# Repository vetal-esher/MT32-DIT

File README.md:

# MT32-DIT
<h3>Adding digital output to legendary Roland MT-32</h3>
<p>Project status: ⬛⬛⬛⬛⬛⬛⬛⬛⬛⬛⬛⬛⬜ 95%</p>
<p>
This project can be considered part #2 of the digitalization of old synthesizers. In the first part I described <a href="https://github.com/vetal-esher/18bit-DIT">how you can add a  digital outpu</a>t to almost any synthesizer (where the DAC circuit uses standard L/R combined I2S) by using the AK4103AVF</p>

<p>
Roland MT-32, familiar to old gamers in the 90s and very rare now, is an even older device that uses a parallel DAC scheme that was 
quite common in Roland's D-series, which does not just convert the final stereo stream in-line, but also simultaneously performs 
the services of a DAC for the reverb IC.</p>

<h3>Digging demuxer logic</h4>

<p>
It turns out that we do not have direct access to the digital stream containing the final audio data. The PCM54HP receives a stream 
that sequentially contains not only clean left and right channels, but also separate reverb data for the left and right channels. 
It looks something like this (all frames are 16bit, order is assumed): [RSYN1][LSYN1][REV R][REV L][RSYN2][LSYN2][RSYN1][LSYN1][REV R][REV L][RSYN2] [LSYN2] etc.</p>
<p>
The advantage of a parallel DAC is that it works instantly, i.e. there is no delay at all in taking the current values 
from the (essentially) resistor assembly and the next moment doing the task of transforming a completely different picture. <strong>Edit: 
to tell the truth, there IS small delay required to let the output settled the final value.</strong>
</p>
<p>The widely known CD4051 is engaged in demultiplexing all this porridge of audio data. Channel switching in the CD4051 is carried out 
through the control lines mixed from LA and Reverb chips SH1 SH2 SH2 (SH - Sample / Hold), as well as the INH line, which turns on and off 
all channels. At the output of the demuxer, three pairs of analog channels are formed, which are then mixed and undergo final 
processing in a low-pass filter. The LP filter should have a flat amplitude response in the 0-20kHz range and a high attenuation above 20kHz.
</p>

<p>
Bit depth and sampling frequency of MT-32 according to the declared characteristics - 15bit 32kHz. In the first version of MT-32 
(the so-called "old"), the last (actually, LSB) 16th bit at the PCM54HP input is shorted to ground, and for that (15bit) reason the 14th bit fell out 
in the data bus itself (counting from zero). However, for us, the frame width will always be 16 bits (the 2nd MT-32 version has full 16bit bus). Theoretically, the channel  switching frequency 0-1-2-3-4-5-6-7 each time triggers a 0/1 state change in control signal A, so you can 
expect 128kHz on this line,  64kHz on line B, and C with 32kHz respectively. But we don't know the order of the frames. Even if we 
sequentially record all the states of the parallel bus, it will be useless if we do not know the order of switching ABC. In practice, 
without a three-channel oscilloscope, you can try to catch the states of at least two of the three lines (A and C), and then record 
the AB and BC, A and INH sequences in order to further bring the picture into one.
</p>

<p>

So now we know the frame order: [L REV][RSYN2][LSYN2][R REV][RSYN1][LSYN1], [L REV][RSYN2][LSYN2][R REV][RSYN1][LSYN1] .. etc. 
If you listen to these pins in analog, it becomes clear that SYN1 is a clean signal, REV is a reverb return. SYN2 appears to be 
analog as well, but too quiet to be recorded legibly; but since SYN2 is also mixed into the final mix, we'll do that too. 
By the way, if you look at the unused outputs of the CD4051 CH4 and CH5, there will be [almost] crisp 32kHz:

<p>The INH control signal operates at a frequency of 256kHz, which means we will need to read all ports at this frequency. 
Disabling all channels is necessary so that there is no false triggering on rising edges @ABC states, when INH=1 tells us that 
we don’t need to send anything to serial. With INH=0, we must read the bus, and depending on the states of ABC, scatter it to 
the appropriate output. Ideally, we need to define the beginning of frame (we take the highest INH peak for the reference frame)
and mix all L / R frames into two final ones. But for the test, you can start by sending two frames with a clean non-reverberated 
information (RSYN1, LSYN1). At first I thought to bother with the sequence' start detection, but then I omitted this part, because,
even if the logic begins to run in the middle, defining LSYN1 as the end of the sequence we will reset the counters and then start 
working in the correct order. The logic in this case will look something like this (I will use a pseudo-language here with a syntax 
that is clear to everyone):</p>

<pre>
(R,L)=(0,0);
(FLAG_RSYN1,FLAG_LSYN1,FLAG_RSYN2,FLAG_LSYN2,FLAG_RREV,FLAG_LREV)=(0,0,0,0,0,0);
(RSYN1,LSYN1,RSYN2,LSYN2,RREV,LREV)=(0,0,0,0,0,0);
while (256kHz_cycle) {
	input=read(PCM54_parallel);
	A=read(CD4051_A); B=read(CD4051_B); C=read(CD4051_C); INH=read(CD4051_INH);

	#INH==0 enables output
	if (INH==0) {
		if (A==1 && B==1 && C==0) {
			RSYN2=input; FLAG_RSYN2=1; #RSYN2
		}
		elsif (A==0 && B==1 && C==0) {
			LSYN2=input; FLAG_LSYN2=1; #LSYN2
		}
		elsif (A==0 && B==0 && C==1) {
			RREV=input; FLAG_RREV=1;   #RREV
		}
		elsif (A==0 && B==0 && C==0) {
			LREV=input; FLAG_LREV=1;   #LREV
		}
		elsif (A==1 && B==1 && C==1) {
			RSYN1=input; FLAG_RSYN1=1; #RSYN1
		}
		elsif (A==0 && B==1 && C==1) {
			LSYN1=input; 		   #LSYN1 this is the last channel in frame
			(FLAG_RSYN1,FLAG_LSYN1,FLAG_RSYN2,FLAG_LSYN2,FLAG_RREV,FLAG_LREV)=(1,1,1,1,1,1);
		}

		if (FLAG_RSYN1==1 && FLAG_LSYN1==1 && FLAG_RSYN2==1 && FLAG_LSYN2==1 && FLAG_RREV==1 && FLAG_LREV==1) {

			#in merge there will be magic
			L=merge(LSYN1,LSYN2,LREV);
			R=merge(RSYN1,RSYN2,RREV);
			write_serial(R,L); 

			#reset channel flags
			(FLAG_RSYN1,FLAG_LSYN1,FLAG_RSYN2,FLAG_LSYN2,FLAG_RREV,FLAG_LREV)=(0,0,0,0,0,0);
		}
	}
}
</pre>

<h3>Hardware part</h3>

<p>Schematically, the plan of the entire project was drawn like this:</p>

<p>
There is only one magic figure involved in this plan, and here, I will honestly say, giant constructions of logic which must perform the task of mixing digital streams comes to mind. I was told that I should stop doing garbage and learn a programmable FPGA. All of the DAC and INH/A/B/C signals are CMOS-level, so we need to convert them to TTL by CD4050B. By the way, we will get fixed levels of INH after CD4050:
</p>

<h4>DIT</h4>
<p>
Since we are dealing with 16 bits, a large number of DITs can be used, as they all work at least with 16-bit RJ. For these purposes, I chose DIT4192, because I have it  already available after experimenting with the 18-bit DIT, but you can skip mounting 4192 if you don't have it (details below). Settings are typical:
<table border="1">
<tr><th colspan="2">DIT4192 Hardware mode</th></tr>
<tr><td>Mode operation</td><td>Slave (SYNC and SCLK are inputs)</td></tr>
<tr><td>Format</td><td>16-Bit Right-Justified</td></tr>
<tr><td>Sampling frequency</td><td>32kHz</td></tr>
<tr><td>Master clock</td><td>16.384MHz (512*fs)</td></tr>
<tr><td>Bit clock</td><td>1.024MHz (16*2*32KHz)</td></tr>
</table>
</p>

<h3>Magic part</h3>
<p>The FPGA <a href="https://wiki.sipeed.com/hardware/en/tang/Tang-Nano-9K/Nano-9K.html">TangNano9K</a> was chosen for the magic part, so the "profit" plan was drawn:</p>

<p>And then the complete schematic of the "magic" part was done. Note the I2S connector, you can completely skip DIT4192 in schematic and use your favorite external DIT, or even just transport I2S to I2S receiver. I tested I2S with external WM8804 DIT board and it works perfectly.</p>

<h3>Making prototypes</h3>
<p>I started with sandwich-like breadboard, trying to split the CMOS-TTL logic from TangNano. Different methods, using couple of variants (voltage dividers) and CD4050 were tried..</p>

.. and then, when i finally decided to use CD4050, i have projected the PCB. The PCBs were made quick at PCBway factory, and i must say their quality is awesome, even for such pet projects like mine :) 

<p>Final design assumes, that the original PCM54HP will be desoldered from MT-32 mainboard, and then socketed on second footprint right on DIT pcb. After that, MT32-DIT can be soldered or socketed on MT-32 mainboard. But for now, we'll just put on the DIT board right over PCM54HP IC.</p>

<h2>Partlist</h2>
<table border=1>
	<tr><th>Reference</th><th>Total</th><th>Value</th><th>Package</th></tr>
	<tr><td>X1</td><td>1</td><td>16.384MHz</td><td>Oscillator DIP-8</td></tr>
	<tr><td>U1, U2, U3, U5</td><td>4</td><td>CD4050</td><td>SO-16</td></tr>
	<tr><td>U4</td><td>1</td><td>Gowin 9K</td><td></td></tr>
	<tr><td>U6</td><td>1</td><td>PCM54HP**</td><td>DIP-28</td></tr>
	<tr><td>U8</td><td>1</td><td>DIT4192IPW***</td><td>SSOP-28</td></tr>
	<tr><td>U7</td><td>1</td><td>AP1117-33</td><td>SOT223-3_TABPIN2</td></tr>
	<tr><td>U10</td><td>2</td><td>PinHeader 1x28</td><td>P2.54mm</td></tr>
	<tr><td>T1</td><td>1</td><td>PE-65612NL***</td><td>PE-65612NL</td></tr>
	<tr><td>SW1</td><td>1</td><td>PWR SW</td><td>SW_DIP_SPSTx01_P2.54mm</td></tr>
	<tr><td>SW2</td><td>1</td><td>CFG SW***</td><td>SW_DIP_SPSTx05_P2.54mm</td></tr>
	<tr><td>R1, R2, R4, R5, R6, R7, R8</td><td>7</td><td>10K ***</td><td>0402</td></tr>
	<tr><td>R3</td><td>1</td><td>300R ***</td><td>0402</td></tr>
	<tr><td>J1</td><td>1</td><td>PinHeader 1x04</td><td>P2.54mm</td></tr>
	<tr><td>J2, J3***</td><td>2</td><td>PinHeader 1x02</td><td>P2.54mm</td></tr>
	<tr><td>J4</td><td></td><td>DNP*</td><td></td></tr>
	<tr><td>J5</td><td>1</td><td>PinHeader 1x05</td><td>P2.54mm</td></tr>
	<tr><td>C1, C2, C3, C4, C5, C6, C7, C8, C10, C11, C12***, C13***, C14</td><td>13</td><td>0.1uF</td><td>0402</td></tr>
	<tr><td>C15***</td><td>1</td><td>10uF</td><td>0402</td></tr>
	<tr><td>C9</td><td>1</td><td>10-22uF</td><td>CP_EIA-7343-43</td></tr>
</table>
<p>If only specific component can be skipped, it's marked within "Reference" column, otherwise all components can be skipped if mark is in "Value" column.</p>
<p><strong>*</strong> - Do Not Place</p>
<p><strong>**</strong> - optional, no need if DIT pcb soldered on top of the original DAC</p>
<p><strong>***</strong> - optional, no need if DIT4192 is not available and you use external DIT</p>

<h3>Learning VERILOG</h3>

<p>I did not have any experience in designing FPGA projects, and did not knew about verilog language anything. But it appeared, that my pseudo-language logic described above is almost verilog-like! So, after few weeks, the very first working code was written.</p>

<details>
  <summary>First verilog code:</summary>	

<pre>
module top (
        input mclk,             //master clock //pin 51
        input clk_inh,          //256kHz INH clk input //pin 53
        input [2:0] ch_id,      //cd4051 sample/hold controls a/b/c 128/64/32kHz //pin a 77 b 76 c 48
        input [15:0] dac,       //parallel input from dac
	input sys_rst_n,        //reset input
	output wire dtr,        //data ready flag //pin54
        output sdata,           //16bit i2s sdata output  //pin 49
        output wire wclk,       //i2s word select lrck output 32kHz //pin 31
        output wire bck         //i2s bit clock output 1024MHz //pin32
);

wire [31:0] data;

dac_decoder dac1(
	.clk_inh(clk_inh),.ch_id(ch_id),.dac(dac),.data(data),.rst_n(sys_rst_n),.dtr(dtr)
);

i2s_serializer ser1 (
	.mclk(mclk),.sdata(sdata),.wclk(wclk),.bck(bck),.data(data),.rst_n(sys_rst_n)
);

endmodule

module i2s_serializer (
        input mclk,             	//master clock 16.384MHz
	input [31:0] data,		//input channels register 
	input wire rst_n,		//reset button	
	output reg sdata,   	    	//i2s sdata output
        output reg wclk,        	//i2s word select lrck output mclk/512 = 32kHz
        output wire bck         	//[3] bit'mclk. i2s bit clock output 
					//16bit * 2 * 32000 = 1.024 MHz (16.384/16)
);
reg [31:0] mclk_counter;       		//32bit counter
assign bck=mclk_counter[3];     	//1.024MHz divide
reg [31:0] data_buf;			//i2s output buffer 
reg [4:0] cbit;				//0-15 current bit counter
			
initial begin
	mclk_counter<=0; cbit<=0; wclk<=0; data_buf<=0;
end

always  @(posedge mclk,negedge rst_n) begin
	if(!rst_n) begin mclk_counter<=0; end 
	else begin mclk_counter<=mclk_counter+1; end
end

//i2s WCLK=0 left, =1 right
always  @(negedge bck) begin					//send sdata from buffer
	if (wclk==0) begin sdata<=data_buf[31-cbit]; end 	//LSYN send
	else if (wclk==1) begin sdata<=data_buf[15-cbit]; end	//RSYN send
	cbit<=cbit+4'b01;
	if (cbit==15 && wclk==0) 
		begin cbit<=0; wclk<=1; end			//LSYN1 end
	else if (cbit==15 && wclk==1) 
		begin cbit<=0; wclk<=0; data_buf<=data; end 	//RSYN1 end, new buffer read
end
endmodule

module dac_decoder (
	input wire rst_n,
        input clk_inh,          	//256kHz INH clk input
        input [2:0] ch_id,    		//cd4051 sample/hold controls a/b/c
        input [15:0] dac,       	//parallel input from dac
	output reg [31:0] data,		//32 bit
	output reg dtr			//data ready flag
);
reg [15:0] ch0;				//LREV
reg [15:0] ch6;				//RSYN2
reg [15:0] ch2;				//LSYN2
reg [15:0] ch1;				//RREV
reg [15:0] ch7;				//RSYN1
reg [15:0] ch3;				//LSYN1
initial begin
	ch0<=0; ch1<=0; ch2<=0; ch3<=0; ch6<=0; ch7<=0; dtr<=0; data<=0;
end

always  @(negedge clk_inh,negedge rst_n) begin
	if(!rst_n) begin
		dtr<=0; data<=0;
	end 
	else begin
	case (ch_id)
		4 : begin dtr<=0; end 			// empty
		0 : begin dtr<=0; ch0<=dac; end 	// LREV
		6 : begin dtr<=0; ch6<=dac; end 	// RSYN2 
		2 : begin dtr<=0; ch2<=dac; end 	// LSYN2
		5 : begin dtr<=0; end 			// empty
		1 : begin dtr<=0; ch1<=dac; end 	// RREV
		7 : begin dtr<=0; ch7<=dac; end 	// RSYN
		3 : begin dtr<=1; ch3<=dac; data = {dac,ch7}; end // LSYN
	endcase
	end
end
endmodule
</pre>

</details>

The <a href="https://www.youtube.com/watch?v=VIkrG32c1l0">first video</a> of clean capture (sorry for low volume, it was at night) (clean stereo, no reverb).

<h3>Mixing 6 digital channels to stereo pair</h3>

The simplest logic of audio mixing is summing the levels. This works in digital too. Remember, that actual bitwidth of "old" Roland MT-32 is 15 (LSB bit is tied to the GND. So, 
we can use 17-bit buffer to sum all 3 channels. Also i implemented "reverb on/off" switch tied to second button at TangNano9K devboard (first one is RESET button). 
OFFSET parameter used to avoid digital overflow problem when summing all channels.

<pre>
reg signed [15:0] lsyn1, lsyn2, rsyn1, rsyn2, rrev;	//channels from LA32 and Reverb ICs
reg signed [15:0] left,right;
reg signed [16:0] l,r;

initial begin
    data<=0; rrev<=0; rsyn1<=0; lsyn2<=0; rsyn2<=0; 
    l<=0; r<=0; left<=0; right<=0; dtr<=0;
end

localparam signed [15:0] OFFSET = 16'd8192; //Digital DC offset fix

always  @(negedge clk_inh) begin
	if (!rst_n) begin
		data<=0; dtr<=0;
	end else begin
	case (ch_id)
     		7 : begin // RSYN1
			rsyn1<=dac; dtr<=1;
			left <= l[15:0]-OFFSET; right <= r[15:0]-OFFSET;
		    end 
		6 : begin rsyn2<=dac; dtr<=0; end // RSYN2
		5 : begin data<={left,right}; dtr<=0; end // empty
		4 : begin dtr<=1; end // empty
		3 : begin lsyn1<=dac; dtr<=1; end // LSYN1
		2 : begin lsyn2<=dac; dtr<=1; end // LSYN2
		1 : begin rrev<=dac;  dtr<=1; end // RREV
		0 : begin dtr<=0; // LREV
			if (!rev_sw) begin  l<=lsyn1; r<=rsyn1;  end else 
			begin l<=lsyn1+lsyn2+dac; r<=rsyn1+rsyn2+rrev; end
 	     	end 
	endcase
	end
end

</pre>
</details>

<h3>Possible problems</h3>

<h4>Clicks</h4>
<p>At the final stage, i found that the frequency of DTR (the flag that signals about full frame cycle pass) is slightly faster than WCLK (smth about 32.0010kHz@DTR vs exact 32.0000kHz@WCLK). 
I
</p>

<p>The first reason is that you cannot operate with registers with multiple actions in one clock tick. You need pipeline. So, mixing logic with OFFSET must be separated.

Also, within this logic, you need to avoid update output data register when it might be in "read status" at serializer. Setting values need some time to be set, so we don't update the data when it is in stage of reading.

<p>After that, recording more than 3 hours showed that the clicks were gone, completely.</p>

<h4>Desync</h4>
<p>Another problem can appear, there <strong>might be</strong> desync that can produce more clicks than useful audio data. The source of problem is in unstable crystal oscillator - you need to check the DIT pcb for shorts and leakages. </p>

<h4>Digital DC offset</h4>

<p><strong>Updated 15.10.2025</strong></p>
<p><strike>It's seems that there's nothing we can do (at least with 1st revision of MT-32) since DAC's LSB bit is tied to ground and there is 14 bit dropped in DAC schematic. 
When LSB bit will be used, there will be no DC offset at all. After all, i checked the PCB and found that the Bit14(=D14) used in schematic bus between LA32/Reverb/DAC - on real PCB has no route out from 
LA32 and Reverb chips, and the pin 27 (D14) on LA32 has no activity on oscilloscope at all. You can slightly lower DC offset decrementing each sample value by 16384 (that the value of amplitude zero when there's no sound from MT-32), but this will give you only 6dB fix.
</strike></p>
<p><strong>Updated 11.12.2025</strong></p>
<p>
Another update, giving a new hope. It seems, that i work with rare PCB revision (79377310 01) that is surely "old" 15-bit version, but it uses LA32 package from "new" 16-bit version.
It's mentioned, that <strong>"Main Board (7937731001) is completely different from (7937731000) in circuit design. But Main Board (79377310001) from which PHONES jack (JK5) is removed is compatible
with (7937731000). Only (79377310001) will be supplied fore replacement. For MT-32 (prior to SN938999) which has no PHONES jack, PHONES jack (JK5) on Main board (79377310001) must be removed."</strong>
</p>
<p>This means, that there IS missing 14 bit in the bus, but it has to be found at bit 0 (LSB) already. Updates will be coming soon.

</p>

<h4>Post digital LPF processing</h4>

<p><strong>To be continued</strong></p>

<h2>Mounting</h2>

<strong>Bad contact problem.</strong> It was nightmare to spend hours to find the source of noisy sound. After weeks(!) of resultless tries, i found that the way i put the pcb over original DAC is not reliable at all - some pins was not connected . 

<p><strong><a href="audio/clean.mp3">Example of clean sound.</a></strong></p>
<p><strong>And <a href="audio/dirty_1.mp3">this is what you should hear</a> when some bits are not connected</strong></p>

<p>To avoid bad contact problem, the only way is to desolder DAC and socket it on the MT32-DIT pcb. This process is very hard without proper experience. First of all, you need to replace nearby caps with lower profile equivalents. Film caps are perfectly fit this objective. Then desolder the DAC itself.</p>

<p>While replacing the caps, it is time to think about picking A/B/C/INH directly from CD4051 demuxer. When you solder wires directly to DIP-package pins, wires tend to break when they bend, so i decided to solder a small protoboard over CD4051 for easy access to this signals.

<p>I used PBD (2-row) 2.54 female headers for socketing the DIT pcb in DAC place. One row, of course, needs to be removed. Why 2-row? Just because i had much more PBD headers than PBS. You can use PBS if you want. Then socket the PCM54HP on DIT pcb.</p>

<p>Remove the MT-32 board from the case. It's time to drill a hole and mount RCA. Find the place where you want it.</p>

<p>Final picture:</p>

<h3>Links</h3>

<p><a href="https://github.com/vetal-esher/MT32-DIT/blob/main/hardware/datasheets/mt-32_Service_Notes_First_Edition.pdf">Roland MT-32 service notes</a></p>
<p><a href="https://github.com/vetal-esher/MT32-DIT/blob/main/hardware/datasheets/pcm54.pdf">PCM54HP datasheet</a></p>
<p><a href="https://github.com/vetal-esher/MT32-DIT/blob/main/hardware/datasheets/hd14051bp.pdf">4051 datasheet</a></p>
<p><a href="https://github.com/vetal-esher/MT32-DIT/blob/main/hardware/datasheets/cd4050b.pdf">CD4050B datasheet</a></p>
<p><a href="https://github.com/vetal-esher/MT32-DIT/blob/main/hardware/datasheets/dit4192.pdf">DIT4192 datasheet</a></p>
<p><a href="https://github.com/vetal-esher/MT32-DIT/blob/main/hardware/datasheets/I2SBUS.pdf">I2S bus specification</a></p>

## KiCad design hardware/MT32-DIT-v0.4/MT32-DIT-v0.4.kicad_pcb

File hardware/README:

In 0.4 version the project was splitted into two:

1. MT32-DIT-v0.4
Main board designed with TangNano 9K support. 
Small noise reduction mod is also added according to PCM54HP datasheet.
I2S pins moved to top right corner.

2. MT32-DIT-board

Small two-sided board with DIT4192 or WM8804 support. You can solder only one side with preferrable DIT IC and connect into I2S connector @MT32-DIT-module.

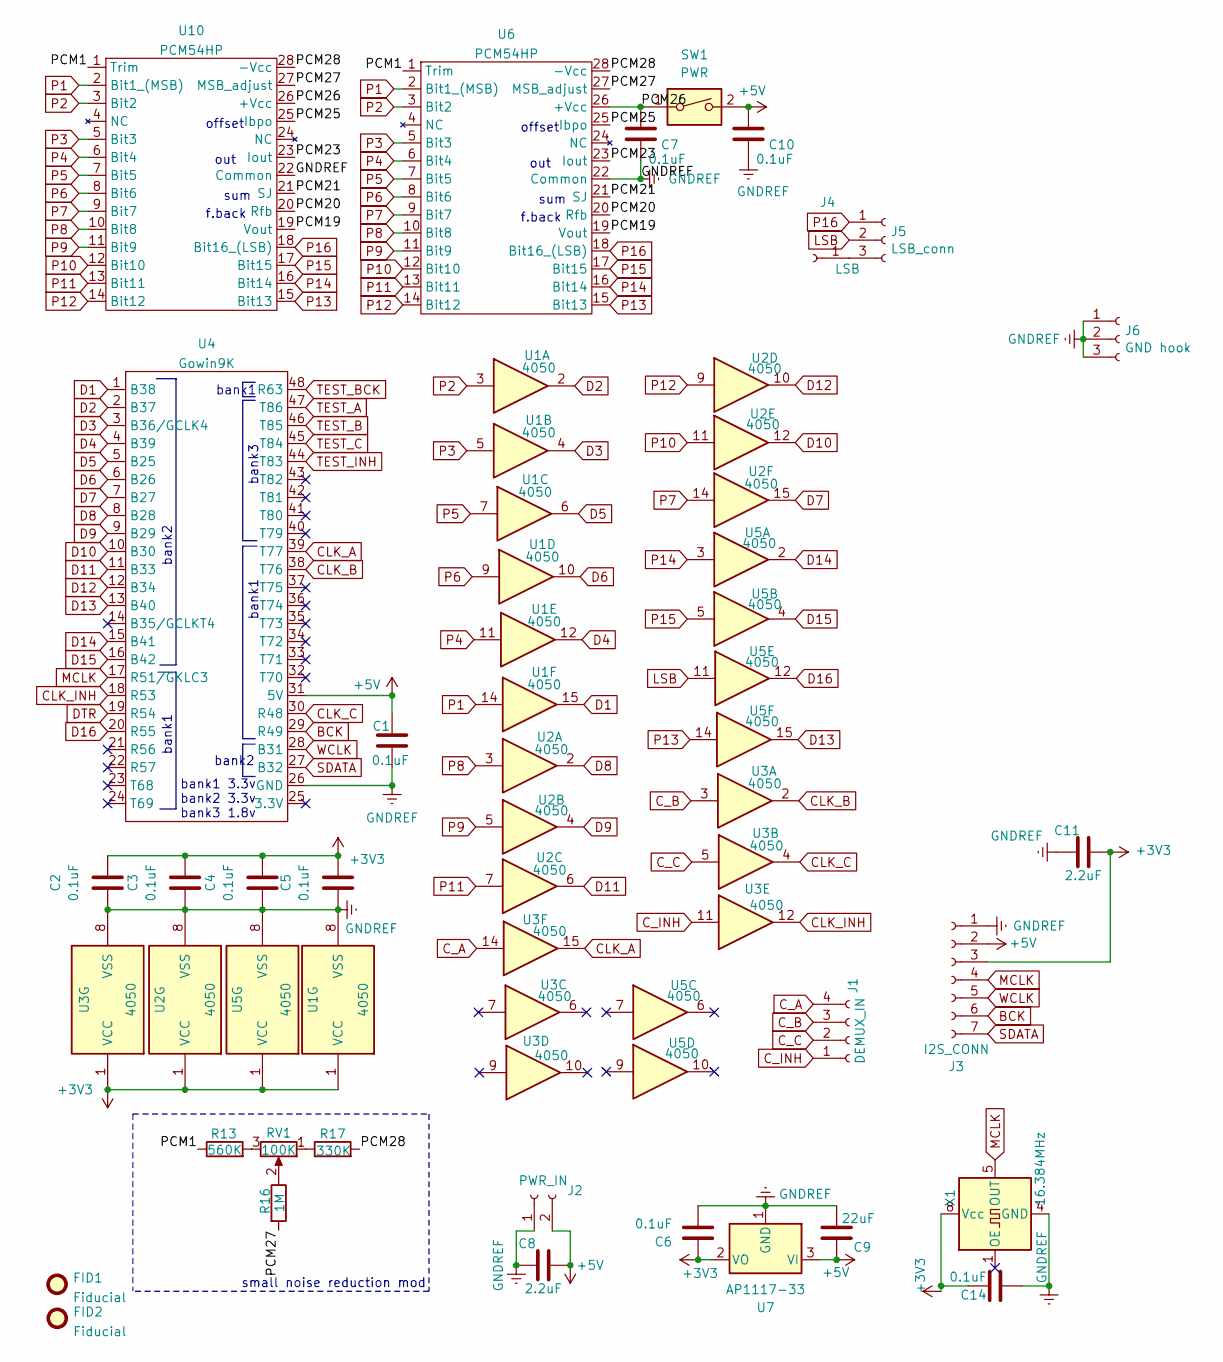
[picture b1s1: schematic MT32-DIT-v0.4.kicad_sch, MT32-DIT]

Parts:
C1, C2, C3, C4, C5, C6, C7, C10, C14: 0.1uF; C_0402_1005Metric_Pad0.74x0.62mm_HandSolder
C8, C11: 2.2uF; C_0603_1608Metric_Pad1.08x0.95mm_HandSolder
C9: 22uF; CP_EIA-7343-43_Kemet-X_Pad2.25x2.55mm_HandSolder
FID1, FID2: Fiducial; Fiducial_0.5mm_Mask1mm
J1: DEMUX_IN; PinHeader_1x04_P2.54mm_Vertical
J2: PWR_IN; PinHeader_1x02_P2.54mm_Vertical
J3: I2S_CONN; PinHeader_1x07_P2.54mm_Vertical
J4: LSB; PinHeader_1x01_P2.54mm_Vertical
J5: LSB_conn; PinHeader_1x03_P2.54mm_Vertical
J6: GND hook; PinHeader_1x03_P2.54mm_Vertical
R13: 560K; R_0402_1005Metric_Pad0.72x0.64mm_HandSolder
R16: 1M; R_0402_1005Metric_Pad0.72x0.64mm_HandSolder
R17: 330K; R_0402_1005Metric_Pad0.72x0.64mm_HandSolder
RV1: 100K; Potentiometer_Piher_PT-6-H_Horizontal
SW1: PWR; SW_DIP_SPSTx01_Slide_6.7x4.1mm_W7.62mm_P2.54mm_LowProfile
U1, U2, U3, U5: 4050; SO-16_3.9x9.9mm_P1.27mm
U4: Gowin9K; DIP-48_W15.24mm_Socket
U6, U10: PCM54HP; PCM54
U7: AP1117-33; SOT-223-3_TabPin2
X1: 16.384MHz; Oscillator_DIP-8

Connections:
+3V3: C2.1, C3.1, C4.1, C5.1, C6.1, C11.2, C14.2, J3.3, U1.1 (VCC), U2.1 (VCC), U3.1 (VCC), U5.1 (VCC), U7.2 (VO), X1.8 (Vcc)
+5V: C1.2, C8.2, C9.1, C10.1, J2.2, J3.2, SW1.2, U4.31 (5V), U7.3 (VI)
/PCM1: R13.1, U6.1 (Trim), U10.1 (Trim)
/PCM19: U6.19 (Vout), U10.19 (Vout)
/PCM20: U6.20 (Rfb), U10.20 (Rfb)
/PCM21: U6.21 (SJ), U10.21 (SJ)
/PCM23: U6.23 (Iout), U10.23 (Iout)
/PCM25: U6.25 (Ibpo), U10.25 (Ibpo)
/PCM26: C7.1, SW1.1, U6.26 (+Vcc), U10.26 (+Vcc)
/PCM27: R16.2, U6.27 (MSB_adjust), U10.27 (MSB_adjust)
/PCM28: R17.2, U6.28 (-Vcc), U10.28 (-Vcc)
BCK: J3.6, U4.29 (R49)
CLK_A: U3.15, U4.39 (T77)
CLK_B: U3.2, U4.38 (T76)
CLK_C: U3.4, U4.30 (R48)
CLK_INH: U3.12, U4.18 (R53)
C_A: J1.4, U3.14
C_B: J1.3, U3.3
C_C: J1.2, U3.5
C_INH: J1.1, U3.11
D1: U1.15, U4.1 (B38)
D2: U1.2, U4.2 (B37)
D3: U1.4, U4.3 (B36/GCLK4)
D4: U1.12, U4.4 (B39)
D5: U1.6, U4.5 (B25)
D6: U1.10, U4.6 (B26)
D7: U2.15, U4.7 (B27)
D8: U2.2, U4.8 (B28)
D9: U2.4, U4.9 (B29)
D10: U2.12, U4.10 (B30)
D11: U2.6, U4.11 (B33)
D12: U2.10, U4.12 (B34)
D13: U4.13 (B40), U5.15
D14: U4.15 (B41), U5.2
D15: U4.16 (B42), U5.4
D16: U4.20 (R55), U5.12
DTR: U4.19 (R54)
GNDREF: C1.1, C2.2, C3.2, C4.2, C5.2, C6.2, C7.2, C8.1, C9.2, C10.2, C11.1, C14.1, J2.1, J3.1, J6.1, J6.2, J6.3, U1.8 (VSS), U2.8 (VSS), U3.8 (VSS), U4.26 (GND), U5.8 (VSS), U6.22 (Common), U7.1 (GND), U10.22 (Common), X1.4 (GND)
LSB: J5.2, U5.11
MCLK: J3.4, U4.17 (R51/GKLC3), X1.5 (OUT)
unnamed: J4.1, J5.3
unnamed: R13.2, RV1.3
unnamed: R16.1, RV1.2
unnamed: R17.1, RV1.1
P1: U1.14, U6.2 (Bit1_(MSB)), U10.2 (Bit1_(MSB))
P2: U1.3, U6.3 (Bit2), U10.3 (Bit2)
P3: U1.5, U6.5 (Bit3), U10.5 (Bit3)
P4: U1.11, U6.6 (Bit4), U10.6 (Bit4)
P5: U1.7, U6.7 (Bit5), U10.7 (Bit5)
P6: U1.9, U6.8 (Bit6), U10.8 (Bit6)
P7: U2.14, U6.9 (Bit7), U10.9 (Bit7)
P8: U2.3, U6.10 (Bit8), U10.10 (Bit8)
P9: U2.5, U6.11 (Bit9), U10.11 (Bit9)
P10: U2.11, U6.12 (Bit10), U10.12 (Bit10)
P11: U2.7, U6.13 (Bit11), U10.13 (Bit11)
P12: U2.9, U6.14 (Bit12), U10.14 (Bit12)
P13: U5.14, U6.15 (Bit13), U10.15 (Bit13)
P14: U5.3, U6.16 (Bit14), U10.16 (Bit14)
P15: U5.5, U6.17 (Bit15), U10.17 (Bit15)
P16: J5.1, U6.18 (Bit16_(LSB)), U10.18 (Bit16_(LSB))
SDATA: J3.7, U4.27 (B32)
TEST_A: U4.47 (T86)
TEST_B: U4.46 (T85)
TEST_BCK: U4.48 (R63)
TEST_C: U4.45 (T84)
TEST_INH: U4.44 (T83)
WCLK: J3.5, U4.28 (B31)

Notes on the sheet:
sum
f.back
offset
out
bank3
bank2
small noise reduction mod
bank1 3.3v bank2 3.3v bank3 1.8v
bank1

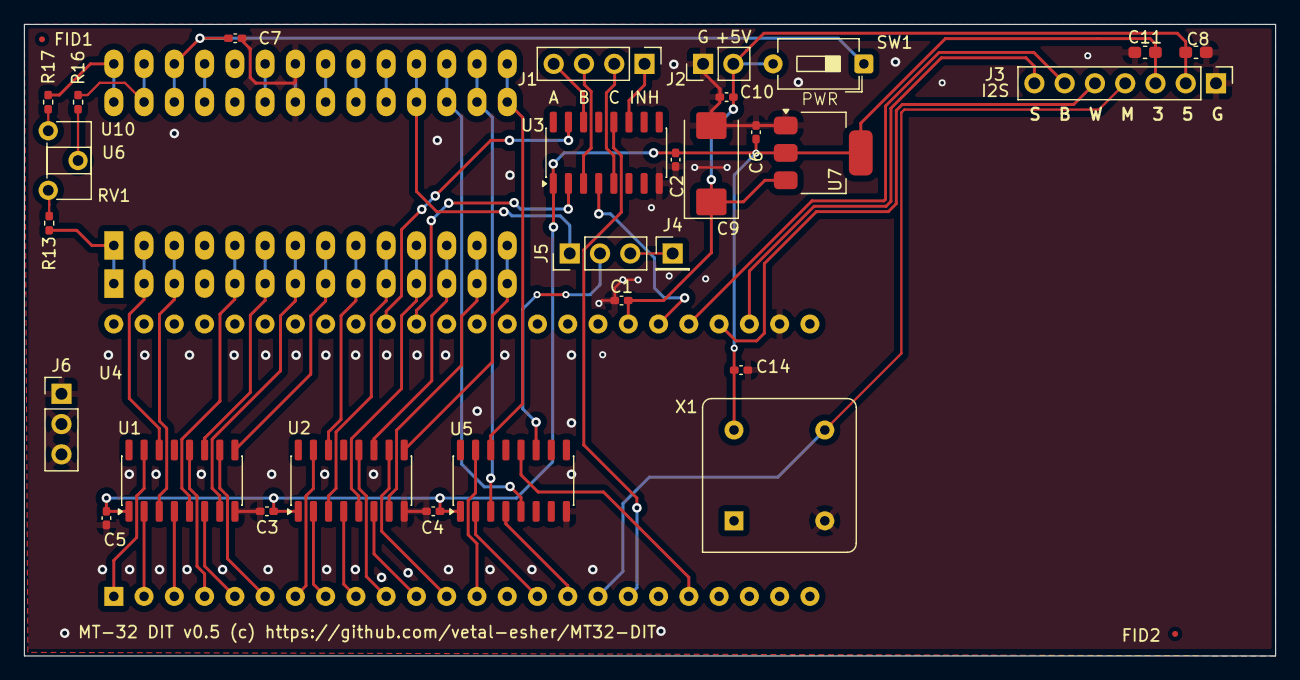
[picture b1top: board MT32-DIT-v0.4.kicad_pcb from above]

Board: 2 copper layers, 105.0 x 53.0 mm, 34 parts (0 on the bottom side), 61 nets.

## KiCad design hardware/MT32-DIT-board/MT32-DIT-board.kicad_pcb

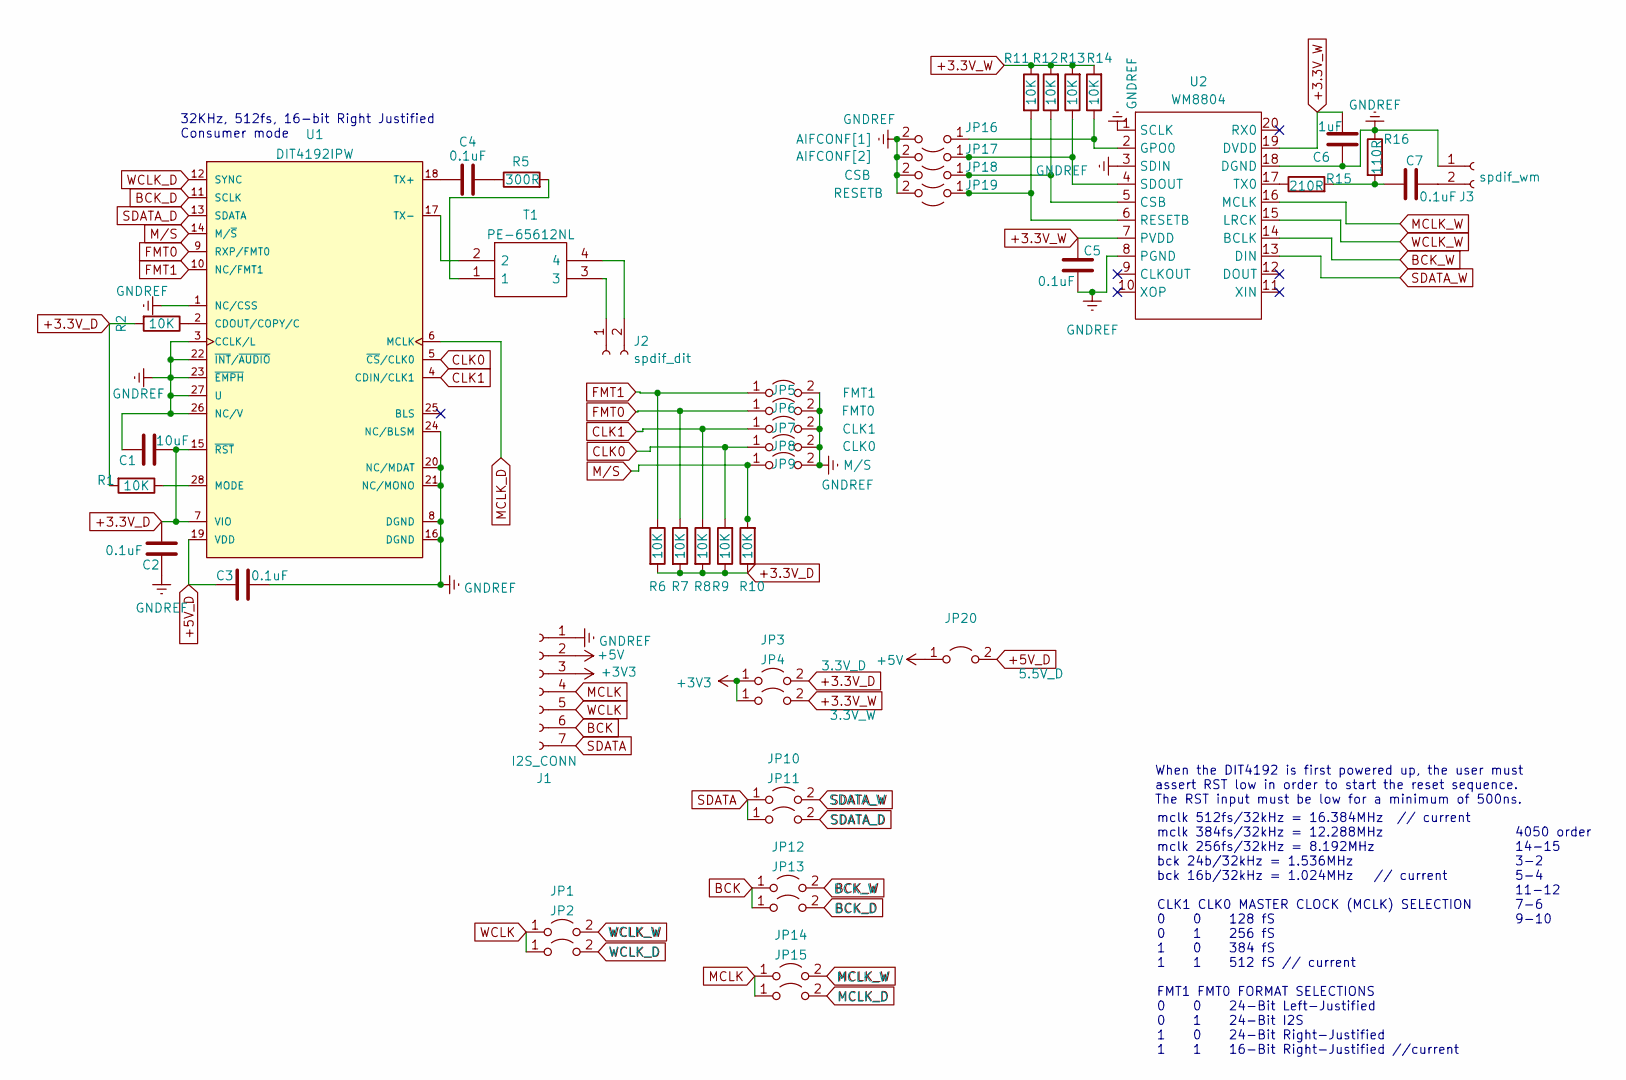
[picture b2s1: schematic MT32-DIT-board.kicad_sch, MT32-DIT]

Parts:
C1: 10uF; C_0402_1005Metric_Pad0.74x0.62mm_HandSolder
C2, C3, C4, C5, C7: 0.1uF; C_0402_1005Metric_Pad0.74x0.62mm_HandSolder
C6: 1uF; C_0603_1608Metric_Pad1.08x0.95mm_HandSolder
J1: I2S_CONN; PinHeader_1x07_P2.54mm_Vertical
J2: spdif_dit; PinHeader_1x02_P2.54mm_Vertical
J3: spdif_wm; PinHeader_1x02_P2.54mm_Vertical
JP1: WCLK_W; SolderJumper-2_P1.3mm_Open_Pad1.0x1.5mm
JP2: WCLK_D; SolderJumper-2_P1.3mm_Open_Pad1.0x1.5mm
JP3: 3.3V_D; SolderJumper-2_P1.3mm_Open_Pad1.0x1.5mm
JP4: 3.3V_W; SolderJumper-2_P1.3mm_Open_Pad1.0x1.5mm
JP5: FMT1; SolderJumper-2_P1.3mm_Open_Pad1.0x1.5mm
JP6: FMT0; SolderJumper-2_P1.3mm_Open_Pad1.0x1.5mm
JP7: CLK1; SolderJumper-2_P1.3mm_Open_Pad1.0x1.5mm
JP8: CLK0; SolderJumper-2_P1.3mm_Open_Pad1.0x1.5mm
JP9: M/S; SolderJumper-2_P1.3mm_Open_Pad1.0x1.5mm
JP10: SDATA_W; SolderJumper-2_P1.3mm_Open_Pad1.0x1.5mm
JP11: SDATA_D; SolderJumper-2_P1.3mm_Open_Pad1.0x1.5mm
JP12: BCK_W; SolderJumper-2_P1.3mm_Open_Pad1.0x1.5mm
JP13: BCK_D; SolderJumper-2_P1.3mm_Open_Pad1.0x1.5mm
JP14: MCLK_W; SolderJumper-2_P1.3mm_Open_Pad1.0x1.5mm
JP15: MCLK_D; SolderJumper-2_P1.3mm_Open_Pad1.0x1.5mm
JP16: AIFCONF[1]; SolderJumper-2_P1.3mm_Open_Pad1.0x1.5mm
JP17: AIFCONF[2]; SolderJumper-2_P1.3mm_Open_Pad1.0x1.5mm
JP18: CSB; SolderJumper-2_P1.3mm_Open_Pad1.0x1.5mm
JP19: RESETB; SolderJumper-2_P1.3mm_Open_Pad1.0x1.5mm
JP20: 5.5V_D; SolderJumper-2_P1.3mm_Open_Pad1.0x1.5mm
R1, R2, R6, R7, R8, R9, R10, R11, R12, R13, R14: 10K; R_0402_1005Metric_Pad0.72x0.64mm_HandSolder
R5: 300R; R_0402_1005Metric_Pad0.72x0.64mm_HandSolder
R15: 210R; R_0402_1005Metric_Pad0.72x0.64mm_HandSolder
R16: 110R; R_0402_1005Metric_Pad0.72x0.64mm_HandSolder
T1: PE-65612NL; PE65612NL; Manufacturer_Part_Number PE-65612NL; Mouser Part Number 673-PE-65612NL
U1: DIT4192IPW; SSOP-28_3.9x9.9mm_P0.635mm
U2: WM8804; SSOP-20_5.3x7.2mm_P0.65mm

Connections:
+3.3V_D: C1.2, C2.2, JP3.2 (B), R1.2, R2.2, R6.2, R7.2, R8.2, R9.1, R10.1, U1.7 (VIO), U1.15 (~RST)
+3.3V_W: C5.2, C6.1, JP4.2 (B), R11.1, R12.2, R13.2, R14.2, U2.7 (PVDD), U2.19 (DVDD)
+3V3: J1.3, JP3.1 (A), JP4.1 (A)
+5V: J1.2, JP20.1 (A)
+5V_D: C3.1, JP20.2 (B), U1.19 (VDD)
BCK: J1.6, JP12.1 (A), JP13.1 (A)
BCK_D: JP13.2 (B), U1.11 (SCLK)
BCK_W: JP12.2 (B), U2.14 (BCLK)
CLK0: JP8.1 (A), R9.2, U1.5 (~CS/CLK0)
CLK1: JP7.1 (A), R8.1, U1.4 (CDIN/CLK1)
FMT0: JP6.1 (A), R7.1, U1.9 (RXP/FMT0)
FMT1: JP5.1 (A), R6.1, U1.10 (NC/FMT1)
GNDREF: C1.1, C2.1, C3.2, C5.1, C6.2, J1.1, J3.1, JP5.2 (B), JP6.2 (B), JP7.2 (B), JP8.2 (B), JP9.2 (B), JP16.2 (B), JP17.2 (B), JP18.2 (B), JP19.2 (B), R16.1, U1.1 (NC/CSS), U1.3 (CCLK/L), U1.8 (DGND), U1.16 (DGND), U1.20 (NC/MDAT), U1.21 (NC/MONO), U1.22 (~INT/~AUDIO), U1.23 (~EMPH), U1.24 (NC/BLSM), U1.26 (NC/V), U1.27 (U), U2.1 (SCLK), U2.3 (SDIN), U2.8 (PGND), U2.18 (DGND)
MCLK: J1.4, JP14.1 (A), JP15.1 (A)
MCLK_D: JP15.2 (B), U1.6 (MCLK)
MCLK_W: JP14.2 (B), U2.16 (MCLK)
M/S: JP9.1 (A), R10.2, U1.14 (M/~S)
unnamed: C4.1, R5.1
unnamed: C7.2, R15.2, R16.2
unnamed: J2.1, T1.3
unnamed: J2.2, T1.4
unnamed: C7.1, J3.2
unnamed: JP16.1 (A), R14.1, U2.2 (GPO0)
unnamed: JP17.1 (A), R13.1, U2.4 (SDOUT)
unnamed: JP18.1 (A), R12.1, U2.5 (CSB)
unnamed: JP19.1 (A), R11.2, U2.6 (RESETB)
unnamed: R5.2, T1.1
unnamed: R2.1, U1.2 (CDOUT/COPY/C)
unnamed: R1.1, U1.28 (MODE)
unnamed: C4.2, U1.18 (TX+)
unnamed: T1.2, U1.17 (TX-)
unnamed: R15.1, U2.17 (TX0)
SDATA: J1.7, JP10.1 (A), JP11.1 (A)
SDATA_D: JP11.2 (B), U1.13 (SDATA)
SDATA_W: JP10.2 (B), U2.13 (DIN)
WCLK: J1.5, JP1.1 (A), JP2.1 (A)
WCLK_D: JP2.2 (B), U1.12 (SYNC)
WCLK_W: JP1.2 (B), U2.15 (LRCK)

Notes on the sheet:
mclk 512fs/32kHz = 16.384MHz // current mclk 384fs/32kHz = 12.288MHz mclk 256fs/32kHz = 8.192MHz bck 24b/32kHz = 1.536MHz bck 16b/32kHz = 1.024MHz // current CLK1 CLK0 MASTER CLOCK (MCLK) SELECTION 0 0 128 fS 0 1 256 fS 1 0 384 fS 1 1 512 fS // current FMT1 FMT0 FORMAT SELECTIONS 0 0 24-Bit Left-Ju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
4050 order 14-15 3-2 5-4 11-12 7-6 9-10
32KHz, 512fs, 16-bit Right Justified Consumer mode
When the DIT4192 is first powered up, the user must assert RST low in order to start the reset sequence. The RST input must be low for a minimum of 500ns.

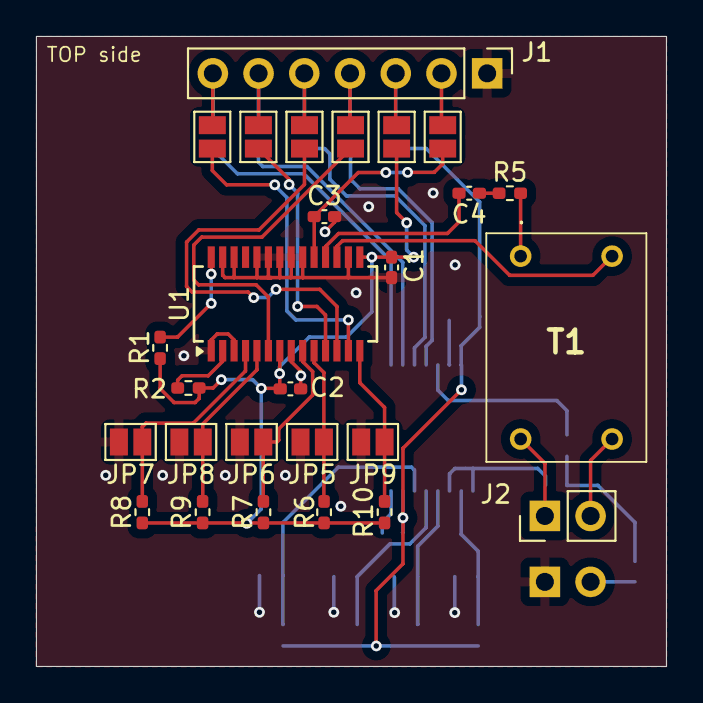
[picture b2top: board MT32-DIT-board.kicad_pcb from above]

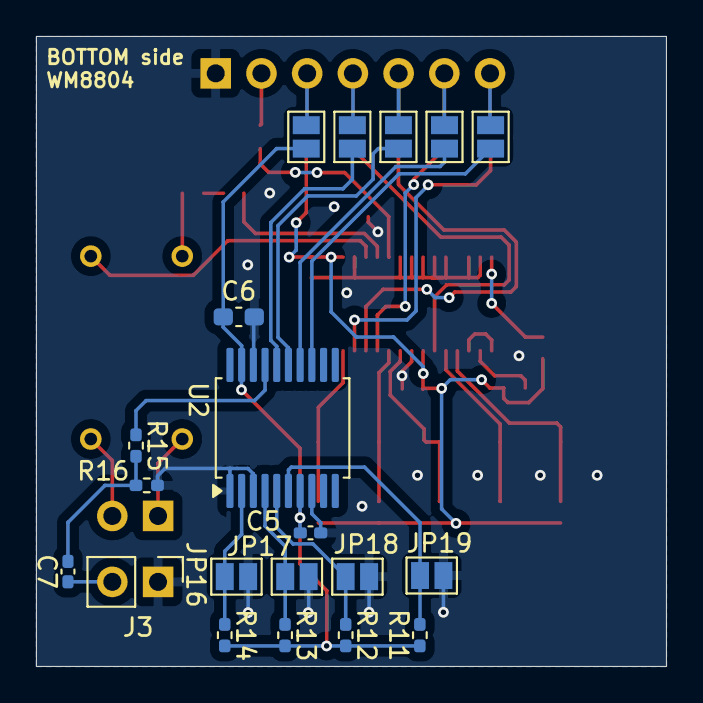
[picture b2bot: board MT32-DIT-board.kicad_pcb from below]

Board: 2 copper layers, 35.0 x 35.0 mm, 47 parts (20 on the bottom side), 38 nets.

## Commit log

2023-03-11 upload montage images
2023-03-11 Datasheets added
2024-06-22 Update README.md
    Added note about digital DC offset.
2024-06-25 Update README.md
    DC offset update
2024-12-06 Add files via upload
    MT32-DIT-module is the main board with FPGA part. Note that the DIT part is splitted into MT32-DIT-board Kicad project.
2024-12-06 Delete hardware/datasheets/MT32-DIT-module directory
    Uploaded by mistake
2024-12-06 Add files via upload
    MT32-DIT-board is the DIT part of the project, small addon card with I2S connector to the MT32-DIT-module.
2024-12-06 Add files via upload
    MT32-DIT-module is the main board with FPGA part which provide I2S output. Small DIT-card with any I2S-to-SPDIF DIT can be designed or MT32-DIT-board can be used.
2024-12-06 Add files via upload
    Verilog project for MT32-DIT.
    MT32-DIT.fs is precompiled firmware to use the pins designed in Kicad.
2024-12-06 Delete hardware/MT32-DIT-module directory
    Found newest project for reupload
2024-12-06 Add files via upload
    MT32-DIT-module FPGA part
2024-12-07 M/S pin was not connected due to Kicad terrible grid, fixed
2025-10-15 Verilog rewrite
    Clean debug pins
    Fix OFFSET as localparam
    Rewrite DAC decoder and I2S serializer
2025-10-15 dac_decoder logics update
    Changes in actions in order of case (ch_id).
    Frame_sent flag added to retry update data register if i2s_serializer is also in update stage (drq is high).
    Added reset switch to mclk cycle.
2025-10-15 Update rst_n logic in dac_decoder
2025-10-22 Update MT32-DIT.v
    DAC frames are now considered as signed.
2025-11-20 Kicad 9.0.5 update
    Kicad update to 9.0.5
    Src change: dtr is back, second buffer register added
2025-11-20 Readme update
    Readme update with latest src changes
2025-12-11 HW updates
    Service notes 2nd and 3rd editions added. Kicad schematic update - LSB bit route can be selected for external input.
2025-12-11 Update README.md
    Missing 14 bit update.
2026-04-03 1. dac_decoder module removed, now reading DAC at the speed of master clock 2. mclk_counter and cbit registers shrinked to fit their real count limits 3. some cosmetic changes and renames 4. reverb_s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
